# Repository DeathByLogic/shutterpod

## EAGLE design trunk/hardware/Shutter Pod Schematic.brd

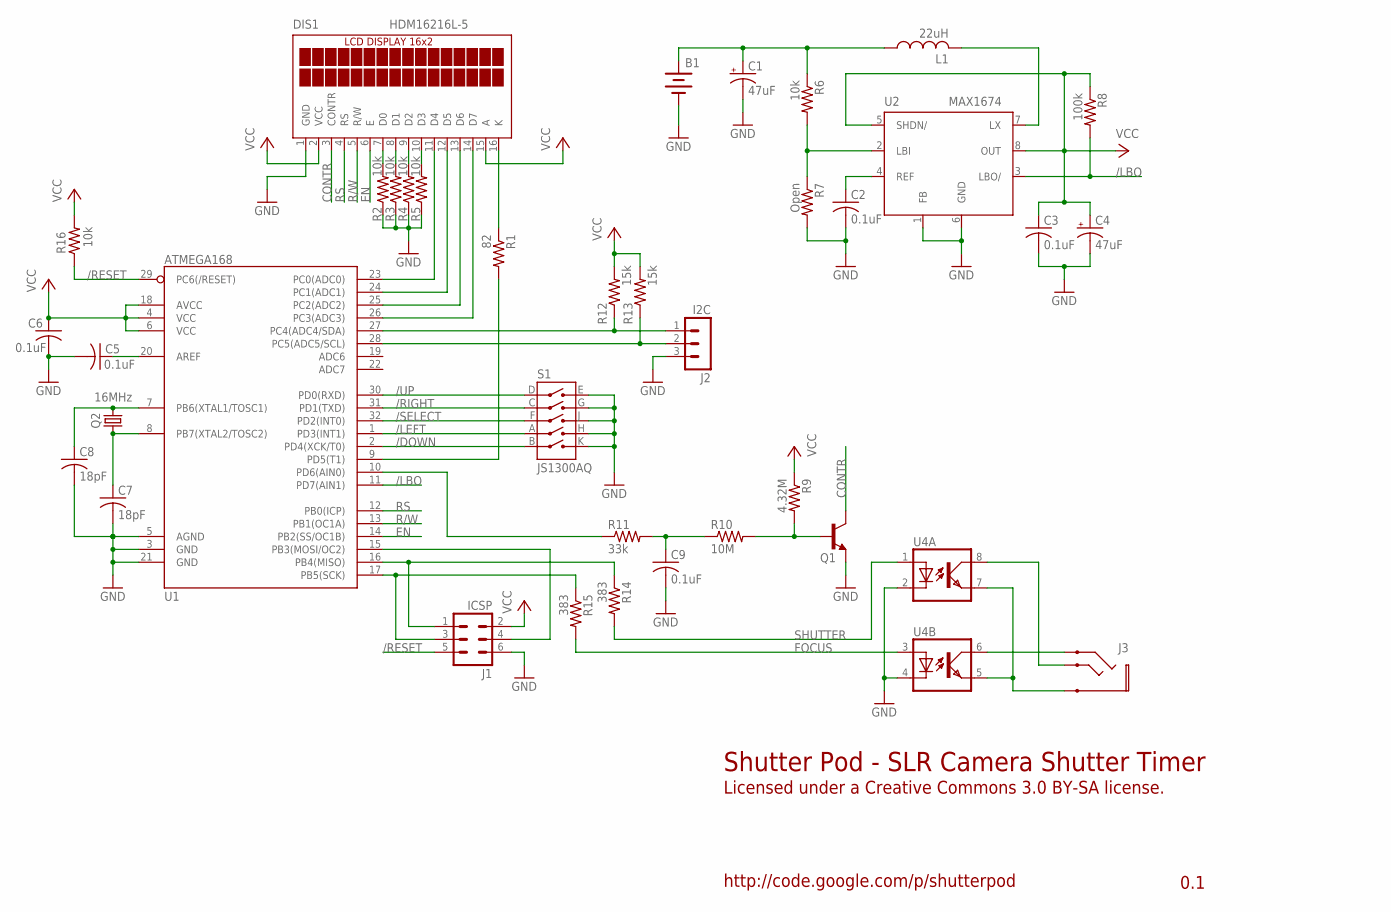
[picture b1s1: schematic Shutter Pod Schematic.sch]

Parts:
B1: BATTERY
C1, C4: 47uF; SMC_D
C2, C3, C5, C6, C9: 0.1uF; C0805
C7, C8: 18pF; C0805
DIS1: HDM16216L-5
J1: ICSP; MA03-2W
J2: I2C; MA03-1W
J3: 2.5MM_AUDIO; 161-2625-E
L1: 22uH; L2220P
Q1: BC817-25SMD; SOT23-BEC
Q2: 16MHz; HC49UP
R1: 82; R0805
R2, R3, R4, R5, R6, R16: 10k; R0805
R7: Open; R0805
R8: 100k; R0805
R9: 4.32M; R0805
R10: 10M; R0805
R11: 33k; R0805
R12, R13: 15k; R0805
R14, R15: 383; R0805
S1: JS1300AQ
U1: ATMEGA168; TQFP32-08
U2: MAX1674; UMAX8
U4: MOCD217M; SO08

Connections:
/DOWN: S1.B, U1.2 (PD4(XCK/T0))
/LBO: R8.2, U1.11 (PD7(AIN1)), U2.3 (LBO/)
/LEFT: S1.A, U1.1 (PD3(INT1))
/RESET: J1.5, R16.1, U1.29 (PC6(/RESET))
/RIGHT: S1.C, U1.31 (PD1(TXD))
/SELECT: S1.F, U1.32 (PD2(INT0))
/UP: S1.D, U1.30 (PD0(RXD))
CONTR: DIS1.3 (CONTR), Q1.C
EN: DIS1.6 (E), U1.14 (PB2(SS/OC1B))
FOCUS: R15.2, U4.3 (A)
GND: B1.1 (NEGATIVE), C1.-, C2.2, C3.2, C4.-, C5.2, C6.2, C7.2, C8.2, C9.2, DIS1.1 (GND), J1.6, J2.3, Q1.E, R2.1, R3.1, R4.1, R5.1, R7.2, S1.E, S1.G, S1.H, S1.J, S1.K, U1.3 (GND), U1.5 (AGND), U1.21 (GND), U2.1 (FB), U2.6 (GND), U4.2 (C), U4.4 (C)
MISO: J1.1, R14.1, U1.16 (PB4(MISO))
MOSI: J1.4, U1.15 (PB3(MOSI/OC2))
unnamed: DIS1.11 (D4), U1.23 (PC0(ADC0))
unnamed: DIS1.12 (D5), U1.24 (PC1(ADC1))
unnamed: DIS1.13 (D6), U1.25 (PC2(ADC2))
unnamed: DIS1.14 (D7), U1.26 (PC3(ADC3))
unnamed: R1.2, U1.9 (PD5(T1))
unnamed: R11.1, U1.10 (PD6(AIN0))
unnamed: Q1.B, R9.2, R10.2
unnamed: DIS1.16 (K), R1.1
unnamed: B1.2 (POSITIVE), C1.+, L1.1, R6.1
unnamed: C5.1, U1.20 (AREF)
unnamed: DIS1.7 (D0), R2.2
unnamed: DIS1.8 (D1), R3.2
unnamed: DIS1.9 (D2), R4.2
unnamed: DIS1.10 (D3), R5.2
unnamed: C2.1, U2.4 (REF)
unnamed: R6.2, R7.1, U2.2 (LBI)
unnamed: C9.1, R10.1, R11.2
unnamed: L1.2, U2.7 (LX)
unnamed: C8.1, Q2.2, U1.7 (PB6(XTAL1/TOSC1))
unnamed: C7.1, Q2.1, U1.8 (PB7(XTAL2/TOSC2))
unnamed: J3.SA (SLEEVE), U4.5 (EMIT), U4.7 (EMIT)
unnamed: J3.T (TIP), U4.8 (COL)
R/W: DIS1.5 (R/W), U1.13 (PB1(OC1A))
RS: DIS1.4 (RS), U1.12 (PB0(ICP))
SCK: J1.3, R15.1, U1.17 (PB5(SCK))
SCL: J2.2, R13.1, U1.28 (PC5(ADC5/SCL))
SDA: J2.1, R12.1, U1.27 (PC4(ADC4/SDA))
SHUTTER: R14.2, U4.1 (A)
VCC: C3.1, C4.+, C6.1, DIS1.2 (VCC), DIS1.15 (A), J1.2, R8.1, R9.1, R12.2, R13.2, R16.2, U1.4 (VCC), U1.6 (VCC), U1.18 (AVCC), U2.5 (SHDN/), U2.8 (OUT)

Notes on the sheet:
0.1
Licensed under a Creative Commons 3.0 BY-SA license.
Shutter Pod - SLR Camera Shutter Timer
http://code.google.com/p/shutterpod

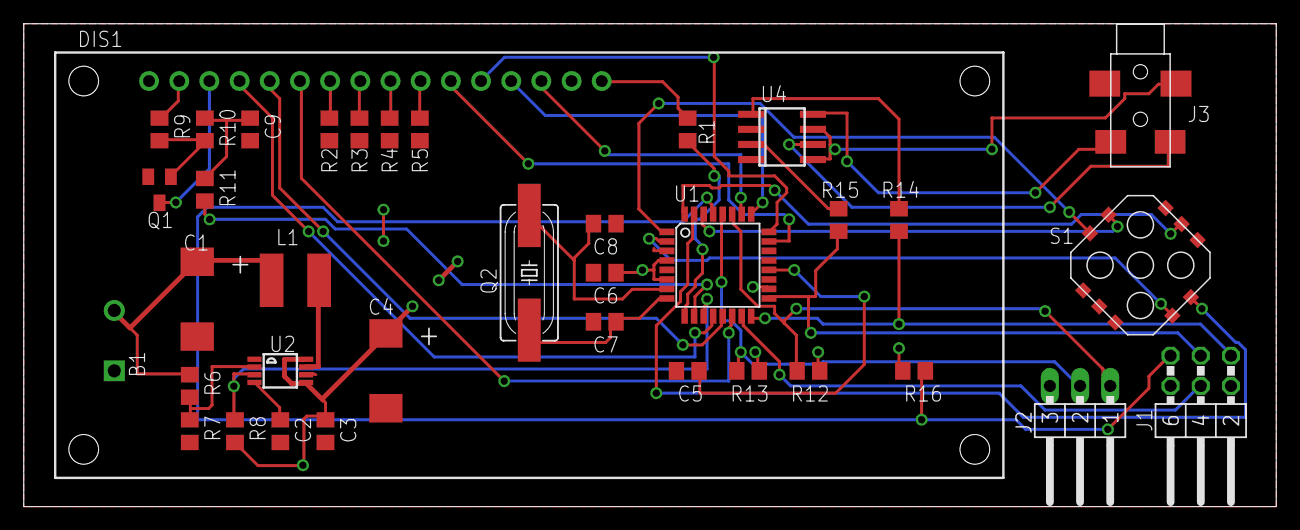
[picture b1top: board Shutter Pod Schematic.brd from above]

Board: 2 copper layers, 105.4 x 40.6 mm, 37 parts (0 on the bottom side), 42 nets.

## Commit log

2010-07-08 Initial directory structure.
2010-07-09 Added initial commit of code from local files.
2010-07-09 Renamed files to proper extension Added GNU public license and header to each file
2010-07-13 Created wiki page through web user interface.
2010-07-13 Edited wiki page through web user interface.
2010-07-13 Initial commit of hardware design
2010-07-15 Cleaned up schematic Added second buffer back to schematic
2010-07-15 Added configuration for PWM output to LED backlight & contrast.
2010-07-24 added opto-couplers for shutter and focus triggers
2010-07-24 Wrote state machine for shutter and focus control. Configured timer 2 for 61.03 Hz clock rate
2010-08-08 Added navigation buttons Updated LCD display symbol
2010-08-21 Edited wiki page PartsList through web user interface.
2010-08-29 Added initial board layout Switched LCD I/O pins Switched navigation button pins Changed Q3 name to Q2 Changed R13, R14 values Changed Q1 part number Changed J1, J2 to right angle headers
2010-09-06 Adjusted pad size for L1, C1 & C4
2010-09-14 Tweaked schematic layout Switched to single comparator package for U3 Added filter capacitor for U3
2010-09-14 Initial commit Gerber files Updated PCB layout
2010-09-14 Fixed I2C labeling mistake on silkscreen
2010-09-15 First release of PCB
2010-09-23 Edited wiki page LCDDisplay through web user interface.
2011-04-21 Initial commit of debounce and fifo
2014-01-13 Added full menu structure to menu.c; Updated camera state machine; Other misc updates.
2014-01-14 Moved camera timer to Timer/Counter1 with frequency of 100 Hz
2014-01-17 misc changes
2014-01-17 Added functions to display and edit time.
2014-04-19 Corrected issue with up button not registering.
2014-04-19 Clarified "if" statement conditions.
2014-04-19 Corrected set_backlight_dc and set_contrast_dc function definitions.
2014-04-19 Added cursor to indicate what time value is being changed; Cleaned up menu code.
2014-05-05 Moved settings to global struct; Added menu items for changing settings; Added functions to display bar; Changed debounce long count to 10; General code cleanup and organization; Added code to change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
2014-05-17 Data bus not defaults to output to reduce power.
2014-05-17 Change default times to values that worked with camera.
2014-05-17 Worked on lowering power usage. - Disabling outputs when not in use - "Shutdown" mode - LCD back-light timeout Moved LCD text into menu.c Cleaned up code for back-light and contrast settings.
2014-05-18 Changed how menu functions (Fewer menus and less clicks to move around)
2014-05-18 Added time delay mode.
2014-05-19 Removed unused files.
2014-05-19 Added code to hide menus for other modes when mode is active.
2014-07-27 Initial commit of version 1 case.
2014-08-18 Spelling corrections; Change contrast range to full available range.
2014-08-19 Added eagle cad library
2014-08-19 Corrected schematic symbol and layout for J3.
2015-01-24 Multiple updates
2015-03-14 Migrating wiki contents from Google Code
